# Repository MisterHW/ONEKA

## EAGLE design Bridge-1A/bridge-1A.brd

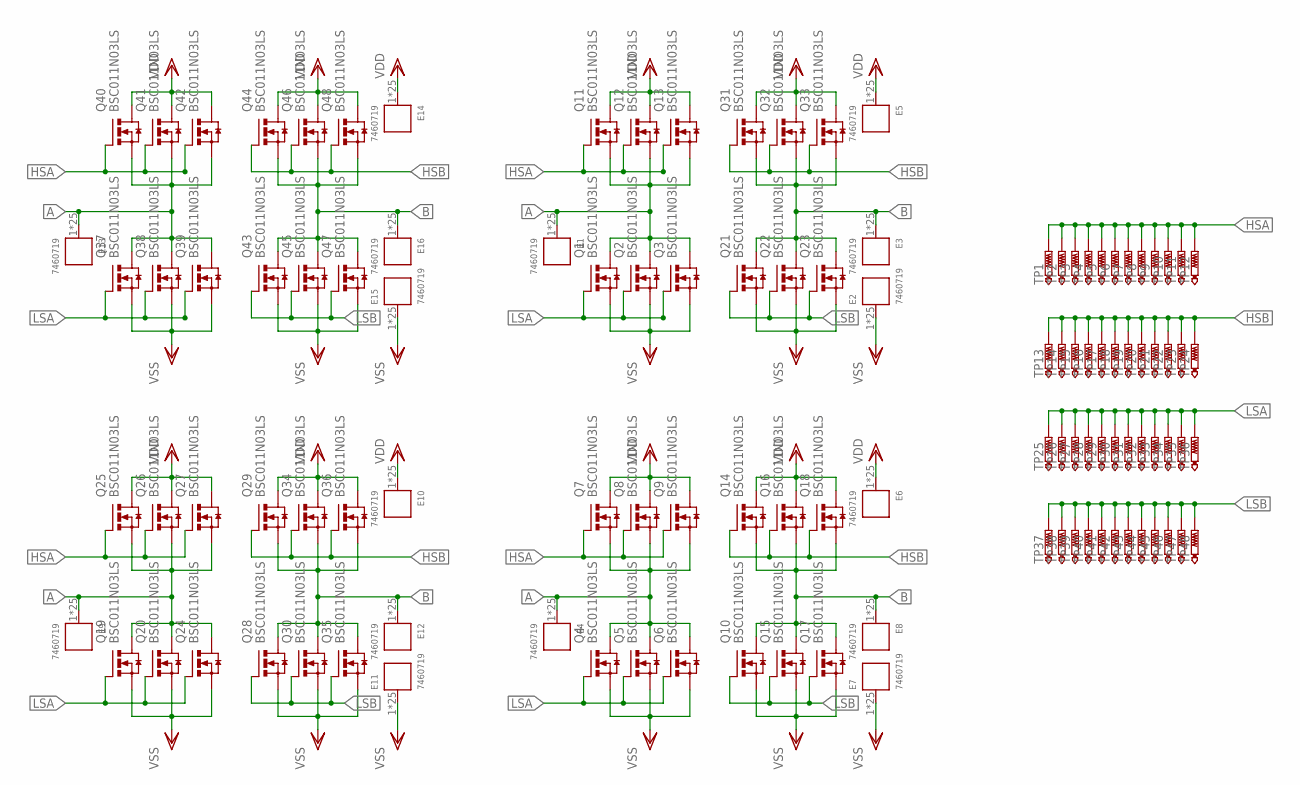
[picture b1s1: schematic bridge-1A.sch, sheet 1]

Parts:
E1, E2, E3, E4, E5, E6, E7, E8, E9, E10, E11, E12, E13, E14, E15, E16: 7460719; 25PINS_FULL_HAL; MF_PARTNO 7460719; MOUSER 710-7460719
Q1, Q2, Q3, Q4, Q5, Q6, Q7, Q8, Q9, Q10, Q11, Q12, Q13, Q14, Q15, Q16, Q17, Q18, Q19, Q20, Q21, Q22, Q23, Q24, Q25, Q26, Q27, Q28, Q29, Q30, Q31, Q32, Q33, Q34, Q35, Q36, Q37, Q38, Q39, Q40, Q41, Q42, Q43, Q44, Q45, Q46, Q47, Q48: BSC011N03LS; PG-TDSON-8
TP1, TP2, TP3, TP4, TP5, TP6, TP7, TP8, TP9, TP10, TP11, TP12, TP13, TP14, TP15, TP16, TP17, TP18, TP19, TP20, TP21, TP22, TP23, TP24, TP25, TP26, TP27, TP28, TP29, TP30, TP31, TP32, TP33, TP34, TP35, TP36, TP37, TP38, TP39, TP40, TP41, TP42, TP43, TP44, TP45, TP46, TP47, TP48: PTR1TP12SQ; TP12SQ

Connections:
A: E1.1, E1.2, E1.3, E1.4, E1.5, E1.6, E1.7, E1.8, E1.9, E1.10, E1.11, E1.12, E1.13, E1.14, E1.15, E1.16, E1.17, E1.18, E1.19, E1.20, E1.21, E1.22, E1.23, E1.24, E1.25, E4.1, E4.2, E4.3, E4.4, E4.5, E4.6, E4.7, E4.8, E4.9, E4.10, E4.11, E4.12, E4.13, E4.14, E4.15, E4.16, E4.17, E4.18, E4.19, E4.20, E4.21, E4.22, E4.23, E4.24, E4.25, E9.1, E9.2, E9.3, E9.4, E9.5, E9.6, E9.7, E9.8, E9.9, E9.10, E9.11, E9.12, E9.13, E9.14, E9.15, E9.16, E9.17, E9.18, E9.19, E9.20, E9.21, E9.22, E9.23, E9.24, E9.25, E13.1, E13.2, E13.3, E13.4, E13.5, E13.6, E13.7, E13.8, E13.9, E13.10, E13.11, E13.12, E13.13, E13.14, E13.15, E13.16, E13.17, E13.18, E13.19, E13.20, E13.21, E13.22, E13.23, E13.24, E13.25, Q1.5 (D), Q1.6 (D), Q1.7 (D), Q1.8 (D), Q1.TH (D), Q2.5 (D), Q2.6 (D), Q2.7 (D), Q2.8 (D), Q2.TH (D), Q3.5 (D), Q3.6 (D), Q3.7 (D), Q3.8 (D), Q3.TH (D), Q4.5 (D), Q4.6 (D), Q4.7 (D), Q4.8 (D), Q4.TH (D), Q5.5 (D), Q5.6 (D), Q5.7 (D), Q5.8 (D), Q5.TH (D), Q6.5 (D), Q6.6 (D), Q6.7 (D), Q6.8 (D), Q6.TH (D), Q7.1 (S), Q7.2 (S), Q7.3 (S), Q8.1 (S), Q8.2 (S), Q8.3 (S), Q9.1 (S), Q9.2 (S), Q9.3 (S), Q11.1 (S), Q11.2 (S), Q11.3 (S), Q12.1 (S), Q12.2 (S), Q12.3 (S), Q13.1 (S), Q13.2 (S), Q13.3 (S), Q19.5 (D), Q19.6 (D), Q19.7 (D), Q19.8 (D), Q19.TH (D), Q20.5 (D), Q20.6 (D), Q20.7 (D), Q20.8 (D), Q20.TH (D), Q24.5 (D), Q24.6 (D), Q24.7 (D), Q24.8 (D), Q24.TH (D), Q25.1 (S), Q25.2 (S), Q25.3 (S), Q26.1 (S), Q26.2 (S), Q26.3 (S), Q27.1 (S), Q27.2 (S), Q27.3 (S), Q37.5 (D), Q37.6 (D), Q37.7 (D), Q37.8 (D), Q37.TH (D), Q38.5 (D), Q38.6 (D), Q38.7 (D), Q38.8 (D), Q38.TH (D), Q39.5 (D), Q39.6 (D), Q39.7 (D), Q39.8 (D), Q39.TH (D), Q40.1 (S), Q40.2 (S), Q40.3 (S), Q41.1 (S), Q41.2 (S), Q41.3 (S), Q42.1 (S), Q42.2 (S), Q42.3 (S)
B: E3.1, E3.2, E3.3, E3.4, E3.5, E3.6, E3.7, E3.8, E3.9, E3.10, E3.11, E3.12, E3.13, E3.14, E3.15, E3.16, E3.17, E3.18, E3.19, E3.20, E3.21, E3.22, E3.23, E3.24, E3.25, E8.1, E8.2, E8.3, E8.4, E8.5, E8.6, E8.7, E8.8, E8.9, E8.10, E8.11, E8.12, E8.13, E8.14, E8.15, E8.16, E8.17, E8.18, E8.19, E8.20, E8.21, E8.22, E8.23, E8.24, E8.25, E12.1, E12.2, E12.3, E12.4, E12.5, E12.6, E12.7, E12.8, E12.9, E12.10, E12.11, E12.12, E12.13, E12.14, E12.15, E12.16, E12.17, E12.18, E12.19, E12.20, E12.21, E12.22, E12.23, E12.24, E12.25, E16.1, E16.2, E16.3, E16.4, E16.5, E16.6, E16.7, E16.8, E16.9, E16.10, E16.11, E16.12, E16.13, E16.14, E16.15, E16.16, E16.17, E16.18, E16.19, E16.20, E16.21, E16.22, E16.23, E16.24, E16.25, Q10.5 (D), Q10.6 (D), Q10.7 (D), Q10.8 (D), Q10.TH (D), Q14.1 (S), Q14.2 (S), Q14.3 (S), Q15.5 (D), Q15.6 (D), Q15.7 (D), Q15.8 (D), Q15.TH (D), Q16.1 (S), Q16.2 (S), Q16.3 (S), Q17.5 (D), Q17.6 (D), Q17.7 (D), Q17.8 (D), Q17.TH (D), Q18.1 (S), Q18.2 (S), Q18.3 (S), Q21.5 (D), Q21.6 (D), Q21.7 (D), Q21.8 (D), Q21.TH (D), Q22.5 (D), Q22.6 (D), Q22.7 (D), Q22.8 (D), Q22.TH (D), Q23.5 (D), Q23.6 (D), Q23.7 (D), Q23.8 (D), Q23.TH (D), Q28.5 (D), Q28.6 (D), Q28.7 (D), Q28.8 (D), Q28.TH (D), Q29.1 (S), Q29.2 (S), Q29.3 (S), Q30.5 (D), Q30.6 (D), Q30.7 (D), Q30.8 (D), Q30.TH (D), Q31.1 (S), Q31.2 (S), Q31.3 (S), Q32.1 (S), Q32.2 (S), Q32.3 (S), Q33.1 (S), Q33.2 (S), Q33.3 (S), Q34.1 (S), Q34.2 (S), Q34.3 (S), Q35.5 (D), Q35.6 (D), Q35.7 (D), Q35.8 (D), Q35.TH (D), Q36.1 (S), Q36.2 (S), Q36.3 (S), Q43.5 (D), Q43.6 (D), Q43.7 (D), Q43.8 (D), Q43.TH (D), Q44.1 (S), Q44.2 (S), Q44.3 (S), Q45.5 (D), Q45.6 (D), Q45.7 (D), Q45.8 (D), Q45.TH (D), Q46.1 (S), Q46.2 (S), Q46.3 (S), Q47.5 (D), Q47.6 (D), Q47.7 (D), Q47.8 (D), Q47.TH (D), Q48.1 (S), Q48.2 (S), Q48.3 (S)
HSA: Q7.4 (G), Q8.4 (G), Q9.4 (G), Q11.4 (G), Q12.4 (G), Q13.4 (G), Q25.4 (G), Q26.4 (G), Q27.4 (G), Q40.4 (G), Q41.4 (G), Q42.4 (G), TP1.TP, TP2.TP, TP3.TP, TP4.TP, TP5.TP, TP6.TP, TP7.TP, TP8.TP, TP9.TP, TP10.TP, TP11.TP, TP12.TP
HSB: Q14.4 (G), Q16.4 (G), Q18.4 (G), Q29.4 (G), Q31.4 (G), Q32.4 (G), Q33.4 (G), Q34.4 (G), Q36.4 (G), Q44.4 (G), Q46.4 (G), Q48.4 (G), TP13.TP, TP14.TP, TP15.TP, TP16.TP, TP17.TP, TP18.TP, TP19.TP, TP20.TP, TP21.TP, TP22.TP, TP23.TP, TP24.TP
LSA: Q1.4 (G), Q2.4 (G), Q3.4 (G), Q4.4 (G), Q5.4 (G), Q6.4 (G), Q19.4 (G), Q20.4 (G), Q24.4 (G), Q37.4 (G), Q38.4 (G), Q39.4 (G), TP25.TP, TP26.TP, TP27.TP, TP28.TP, TP29.TP, TP30.TP, TP31.TP, TP32.TP, TP33.TP, TP34.TP, TP35.TP, TP36.TP
LSB: Q10.4 (G), Q15.4 (G), Q17.4 (G), Q21.4 (G), Q22.4 (G), Q23.4 (G), Q28.4 (G), Q30.4 (G), Q35.4 (G), Q43.4 (G), Q45.4 (G), Q47.4 (G), TP37.TP, TP38.TP, TP39.TP, TP40.TP, TP41.TP, TP42.TP, TP43.TP, TP44.TP, TP45.TP, TP46.TP, TP47.TP, TP48.TP
VDD: E5.1, E5.2, E5.3, E5.4, E5.5, E5.6, E5.7, E5.8, E5.9, E5.10, E5.11, E5.12, E5.13, E5.14, E5.15, E5.16, E5.17, E5.18, E5.19, E5.20, E5.21, E5.22, E5.23, E5.24, E5.25, E6.1, E6.2, E6.3, E6.4, E6.5, E6.6, E6.7, E6.8, E6.9, E6.10, E6.11, E6.12, E6.13, E6.14, E6.15, E6.16, E6.17, E6.18, E6.19, E6.20, E6.21, E6.22, E6.23, E6.24, E6.25, E10.1, E10.2, E10.3, E10.4, E10.5, E10.6, E10.7, E10.8, E10.9, E10.10, E10.11, E10.12, E10.13, E10.14, E10.15, E10.16, E10.17, E10.18, E10.19, E10.20, E10.21, E10.22, E10.23, E10.24, E10.25, E14.1, E14.2, E14.3, E14.4, E14.5, E14.6, E14.7, E14.8, E14.9, E14.10, E14.11, E14.12, E14.13, E14.14, E14.15, E14.16, E14.17, E14.18, E14.19, E14.20, E14.21, E14.22, E14.23, E14.24, E14.25, Q7.5 (D), Q7.6 (D), Q7.7 (D), Q7.8 (D), Q7.TH (D), Q8.5 (D), Q8.6 (D), Q8.7 (D), Q8.8 (D), Q8.TH (D), Q9.5 (D), Q9.6 (D), Q9.7 (D), Q9.8 (D), Q9.TH (D), Q11.5 (D), Q11.6 (D), Q11.7 (D), Q11.8 (D), Q11.TH (D), Q12.5 (D), Q12.6 (D), Q12.7 (D), Q12.8 (D), Q12.TH (D), Q13.5 (D), Q13.6 (D), Q13.7 (D), Q13.8 (D), Q13.TH (D), Q14.5 (D), Q14.6 (D), Q14.7 (D), Q14.8 (D), Q14.TH (D), Q16.5 (D), Q16.6 (D), Q16.7 (D), Q16.8 (D), Q16.TH (D), Q18.5 (D), Q18.6 (D), Q18.7 (D), Q18.8 (D), Q18.TH (D), Q25.5 (D), Q25.6 (D), Q25.7 (D), Q25.8 (D), Q25.TH (D), Q26.5 (D), Q26.6 (D), Q26.7 (D), Q26.8 (D), Q26.TH (D), Q27.5 (D), Q27.6 (D), Q27.7 (D), Q27.8 (D), Q27.TH (D), Q29.5 (D), Q29.6 (D), Q29.7 (D), Q29.8 (D), Q29.TH (D), Q31.5 (D), Q31.6 (D), Q31.7 (D), Q31.8 (D), Q31.TH (D), Q32.5 (D), Q32.6 (D), Q32.7 (D), Q32.8 (D), Q32.TH (D), Q33.5 (D), Q33.6 (D), Q33.7 (D), Q33.8 (D), Q33.TH (D), Q34.5 (D), Q34.6 (D), Q34.7 (D), Q34.8 (D), Q34.TH (D), Q36.5 (D), Q36.6 (D), Q36.7 (D), Q36.8 (D), Q36.TH (D), Q40.5 (D), Q40.6 (D), Q40.7 (D), Q40.8 (D), Q40.TH (D), Q41.5 (D), Q41.6 (D), Q41.7 (D), Q41.8 (D), Q41.TH (D), Q42.5 (D), Q42.6 (D), Q42.7 (D), Q42.8 (D), Q42.TH (D), Q44.5 (D), Q44.6 (D), Q44.7 (D), Q44.8 (D), Q44.TH (D), Q46.5 (D), Q46.6 (D), Q46.7 (D), Q46.8 (D), Q46.TH (D), Q48.5 (D), Q48.6 (D), Q48.7 (D), Q48.8 (D), Q48.TH (D)
VSS: E2.1, E2.2, E2.3, E2.4, E2.5, E2.6, E2.7, E2.8, E2.9, E2.10, E2.11, E2.12, E2.13, E2.14, E2.15, E2.16, E2.17, E2.18, E2.19, E2.20, E2.21, E2.22, E2.23, E2.24, E2.25, E7.1, E7.2, E7.3, E7.4, E7.5, E7.6, E7.7, E7.8, E7.9, E7.10, E7.11, E7.12, E7.13, E7.14, E7.15, E7.16, E7.17, E7.18, E7.19, E7.20, E7.21, E7.22, E7.23, E7.24, E7.25, E11.1, E11.2, E11.3, E11.4, E11.5, E11.6, E11.7, E11.8, E11.9, E11.10, E11.11, E11.12, E11.13, E11.14, E11.15, E11.16, E11.17, E11.18, E11.19, E11.20, E11.21, E11.22, E11.23, E11.24, E11.25, E15.1, E15.2, E15.3, E15.4, E15.5, E15.6, E15.7, E15.8, E15.9, E15.10, E15.11, E15.12, E15.13, E15.14, E15.15, E15.16, E15.17, E15.18, E15.19, E15.20, E15.21, E15.22, E15.23, E15.24, E15.25, Q1.1 (S), Q1.2 (S), Q1.3 (S), Q2.1 (S), Q2.2 (S), Q2.3 (S), Q3.1 (S), Q3.2 (S), Q3.3 (S), Q4.1 (S), Q4.2 (S), Q4.3 (S), Q5.1 (S), Q5.2 (S), Q5.3 (S), Q6.1 (S), Q6.2 (S), Q6.3 (S), Q10.1 (S), Q10.2 (S), Q10.3 (S), Q15.1 (S), Q15.2 (S), Q15.3 (S), Q17.1 (S), Q17.2 (S), Q17.3 (S), Q19.1 (S), Q19.2 (S), Q19.3 (S), Q20.1 (S), Q20.2 (S), Q20.3 (S), Q21.1 (S), Q21.2 (S), Q21.3 (S), Q22.1 (S), Q22.2 (S), Q22.3 (S), Q23.1 (S), Q23.2 (S), Q23.3 (S), Q24.1 (S), Q24.2 (S), Q24.3 (S), Q28.1 (S), Q28.2 (S), Q28.3 (S), Q30.1 (S), Q30.2 (S), Q30.3 (S), Q35.1 (S), Q35.2 (S), Q35.3 (S), Q37.1 (S), Q37.2 (S), Q37.3 (S), Q38.1 (S), Q38.2 (S), Q38.3 (S), Q39.1 (S), Q39.2 (S), Q39.3 (S), Q43.1 (S), Q43.2 (S), Q43.3 (S), Q45.1 (S), Q45.2 (S), Q45.3 (S), Q47.1 (S), Q47.2 (S), Q47.3 (S)

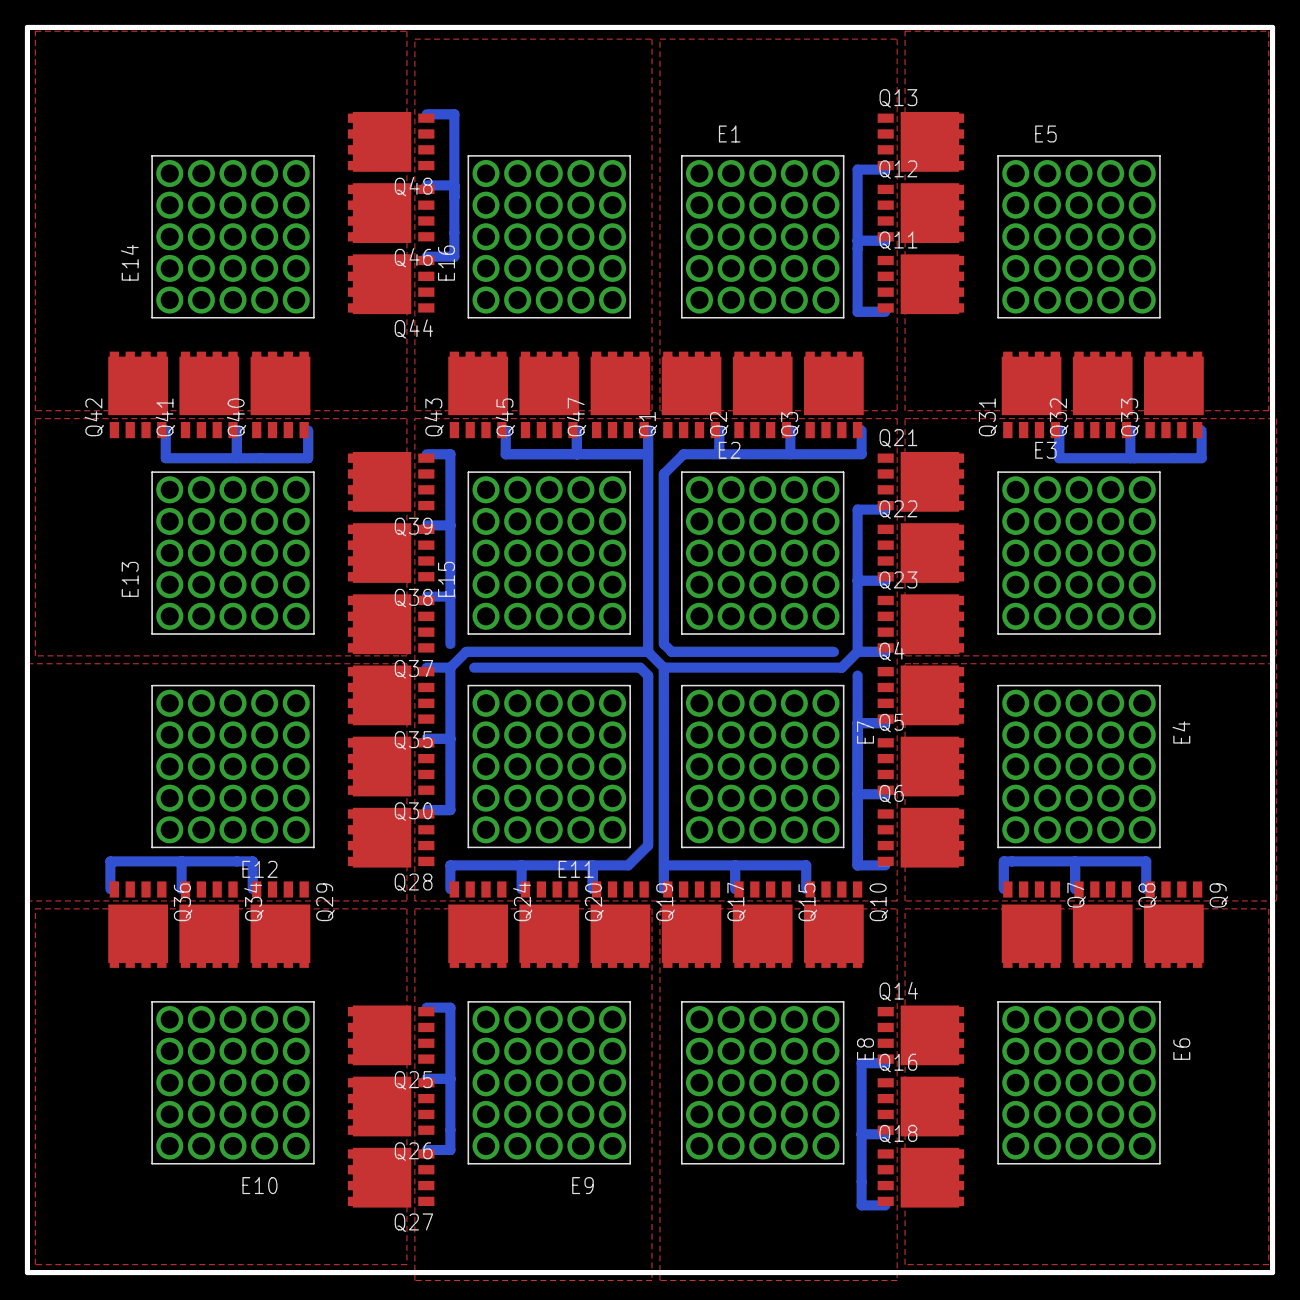
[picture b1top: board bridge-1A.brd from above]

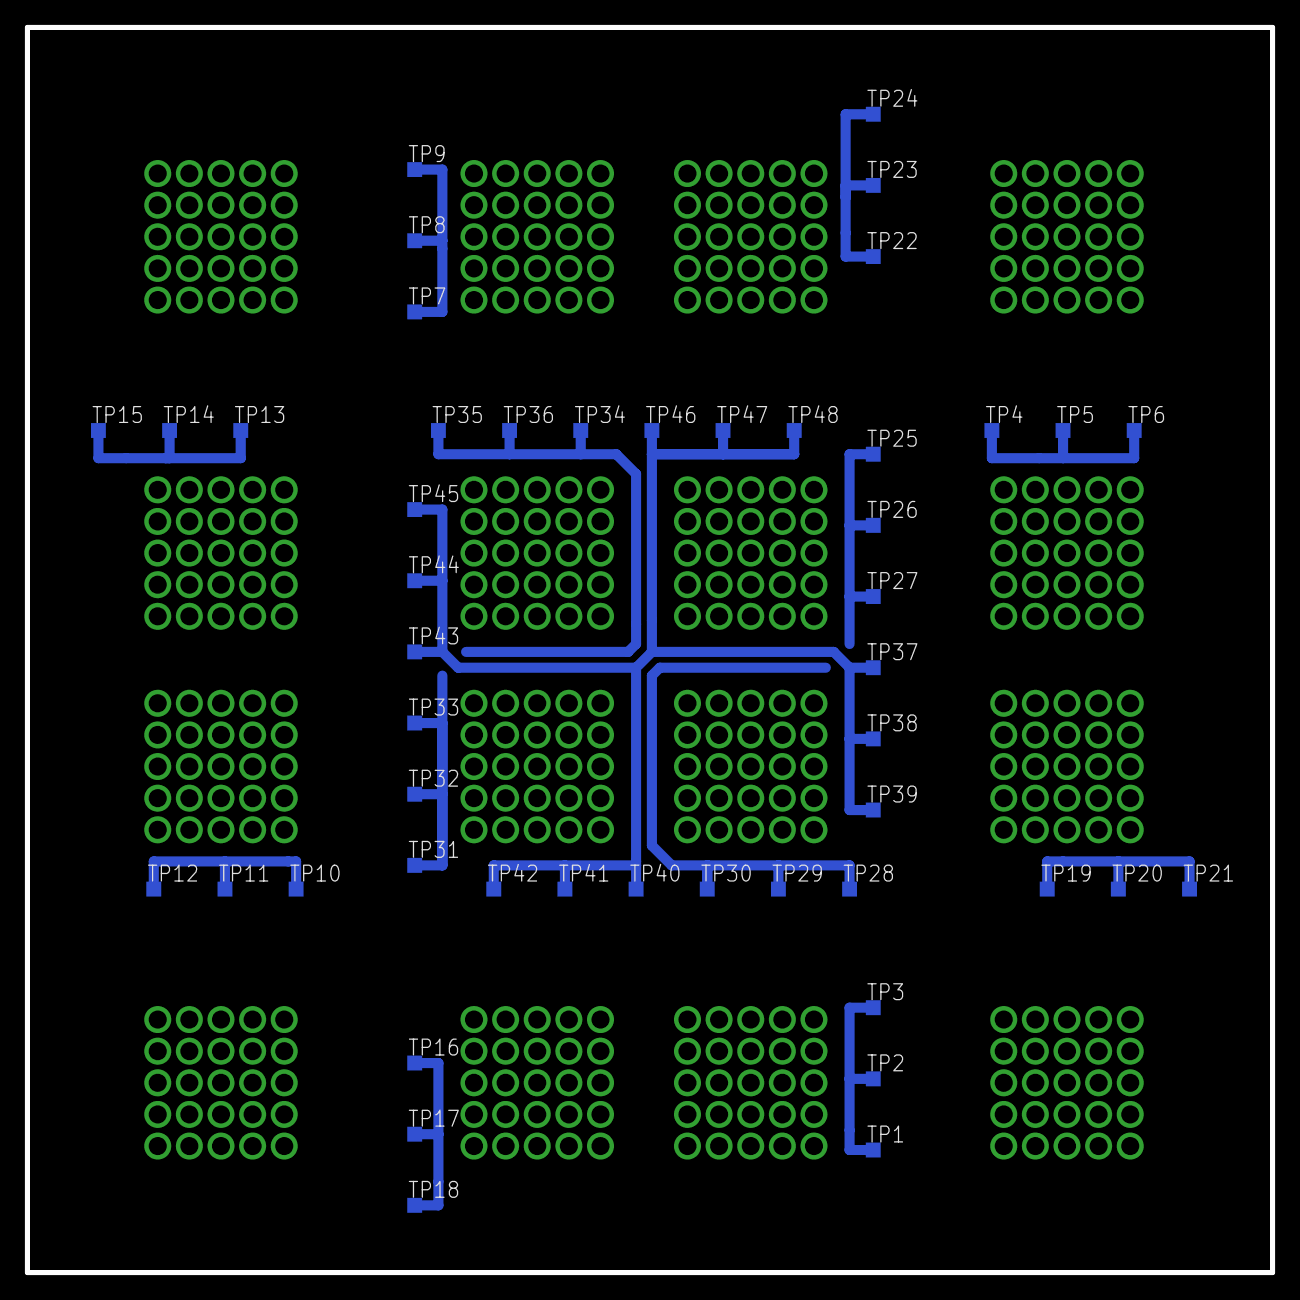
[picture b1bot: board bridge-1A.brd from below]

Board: 2 copper layers, 100.0 x 100.0 mm, 112 parts (48 on the bottom side), 8 nets.

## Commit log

2017-07-09 initial commit of a 30V 1kA full bridge with M8 screw terminals. power traces are milled solid copper tiles (top layer) glued to a copper heat sink with thermal adhesive. Multiple inlays of 0.4mm FR4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

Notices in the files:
parts and their libraries:
Wuerth_Elektronik_Power_Elements_rev15c: Copyright: Würth Elektronik
